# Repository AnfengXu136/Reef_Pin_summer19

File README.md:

# D-SEA: The Depth-Sensor Enclosed Application
## Project Overview
### Abstract
Depth information is crucial in the creation of underwater 3D interactive models. Divers and researchers need depth measurements to accurately depict the structure and levels of underwater architectures for a virtual reality marine ecosystem. Currently, divers are manually measuring the depth using dive watches, but this method is inconsistent because of variable depth readings caused by changing wave heights and human errors.  To combat these problems, we created Depth-Sensor Enclosed Application (D-SEA) to automatically collect and average pressure data while displaying the calculated depth readings with values up to 30 meters underwater which is 3 times more than expected diving conditions. This device can be easily assembled with a cost of under one-hundred dollars.  Building from past developments, we are working on an affordable, waterproof prototype with a display that is readable underwater, an automatic transition between on and off states when submerged in seawater, and automatic data logging onto an SD card. From testing the recent prototype in a pool, results show that the D-SEA is able to accurately calculate the depth and display it on the screen.

### 100 Island Challenge
Our project falls within the greater context of the 100 Island Challenge, headed by the Scripps Institute of Oceanography. The 100 Island Challenge is a project that is collecting photographic, geographic, and oceanographic data in order to build models of coral reef communities around the world and track their changes in structure and growth over time. More information on the challenge can be found [here](http://100islandchallenge.org/).

### Requirements
Researchers from Scripps Institution of Oceanography wish to work with this device under the following conditions: Bring the device on a boat and turn it on before going diving with the corals. Then they dive down and place the devices on the coral reef, and the device starts collecting depth information and displaying it on the screen. The divers swim back and forth to do the photomosaic survey, capturing images of the devices and the data shown on the screen. After that, they collect the devices and return to the boat. They read the data from the devices and download it for backup. Finally, they turn off the device and charge the device overnight.

### Objectives
Based on the requirements from Scripps Institution of Oceanography, we are building a device that can measure and display depth information when it’s placed on coral reefs. Then the depth information could be captured by cameras and retrieved from images. The other detailed functions are described as follows.
* Switch: A switch is needed to make sure the device can turn on before diving and turn off when it’s back to land. 
* Waterproof: Since the device needs to be working under 10-15 meters of salt water for around 4 hours, it should be strictly waterproof to avoid erosion. Waterproof also means that there may not be any buttons or plugs on this device.
* Clear display: The device works in relatively shallow, high-illumination conditions in coral reef communities. There will be sunlight, wind, and wave changing over time. The display module should display the depth information as clear as possible under different conditions to make sure the information can be retrieved from the images accurately.
* Rechargeable: The device needs to be reusable and rechargeable. The battery needs to be working for around 4 hours and can be charged fully over one night.
* Data storage: There may be cases that researchers fail to retrieve accurate depth information from unclear images. For backup consideration, this device should be integrated with a data storage module such as an SD-card.

### Previous Work
GitHub repositories containing work done by the previous teams on this project can be found here. Their works and documentations provided us with valuable guidance for this project.
* [Summer 2018 REU](https://github.com/UCSD-E4E/coral-reef-mapping)
* [Spring 2019 Quarter](https://github.com/ChenLR/SIT)

## Team Members (Summer 2019 Engineers for Exploration)
* Anfeng Xu - UC San Diego
* Brian Sebastian - UC San Diego
* Charmaine Beluso - Mississippi State University
* Eamon Patamasing - UC San Diego

## Resources
* [User Manual](https://docs.google.com/document/d/1ufcVEwToTL347TIJa8BTdMBOQnbh-Dc6tYHnt09aWhc/edit?usp=sharing)
* [Final Report](https://docs.google.com/document/d/1GHIrqxifWv97SIiYkwtMFNrA6XIQ8vvvFCd0-GAbfDE/edit?usp=sharing)
* [Technical Paper]()
* [Final Presentation](https://docs.google.com/presentation/d/16IRXAvVATnhi6VliVaiazFm-Qb-JAyPtN_WVCFj1rOY/edit#slide=id.g3feb1946b7_17_0)
* [Notes for next team](https://docs.google.com/document/d/1U75X6sHqDsNa_K2ptZNxjGdgGvhvemMbGUb-xTKog6w/edit?usp=sharing)
* [Next steps](https://docs.google.com/document/d/1MVm5gGPROugtsDwmIqsRltZwrWXT1dNbkipjWg4ARCg/edit?usp=sharing)

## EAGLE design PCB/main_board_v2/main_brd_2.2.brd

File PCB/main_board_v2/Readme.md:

## PCB files for main board
Includes Eagle files(a .sch and a .brd file), a schematic pdf and a lbr folder containing additional libraries. coral_power.lbr is a custom library file.

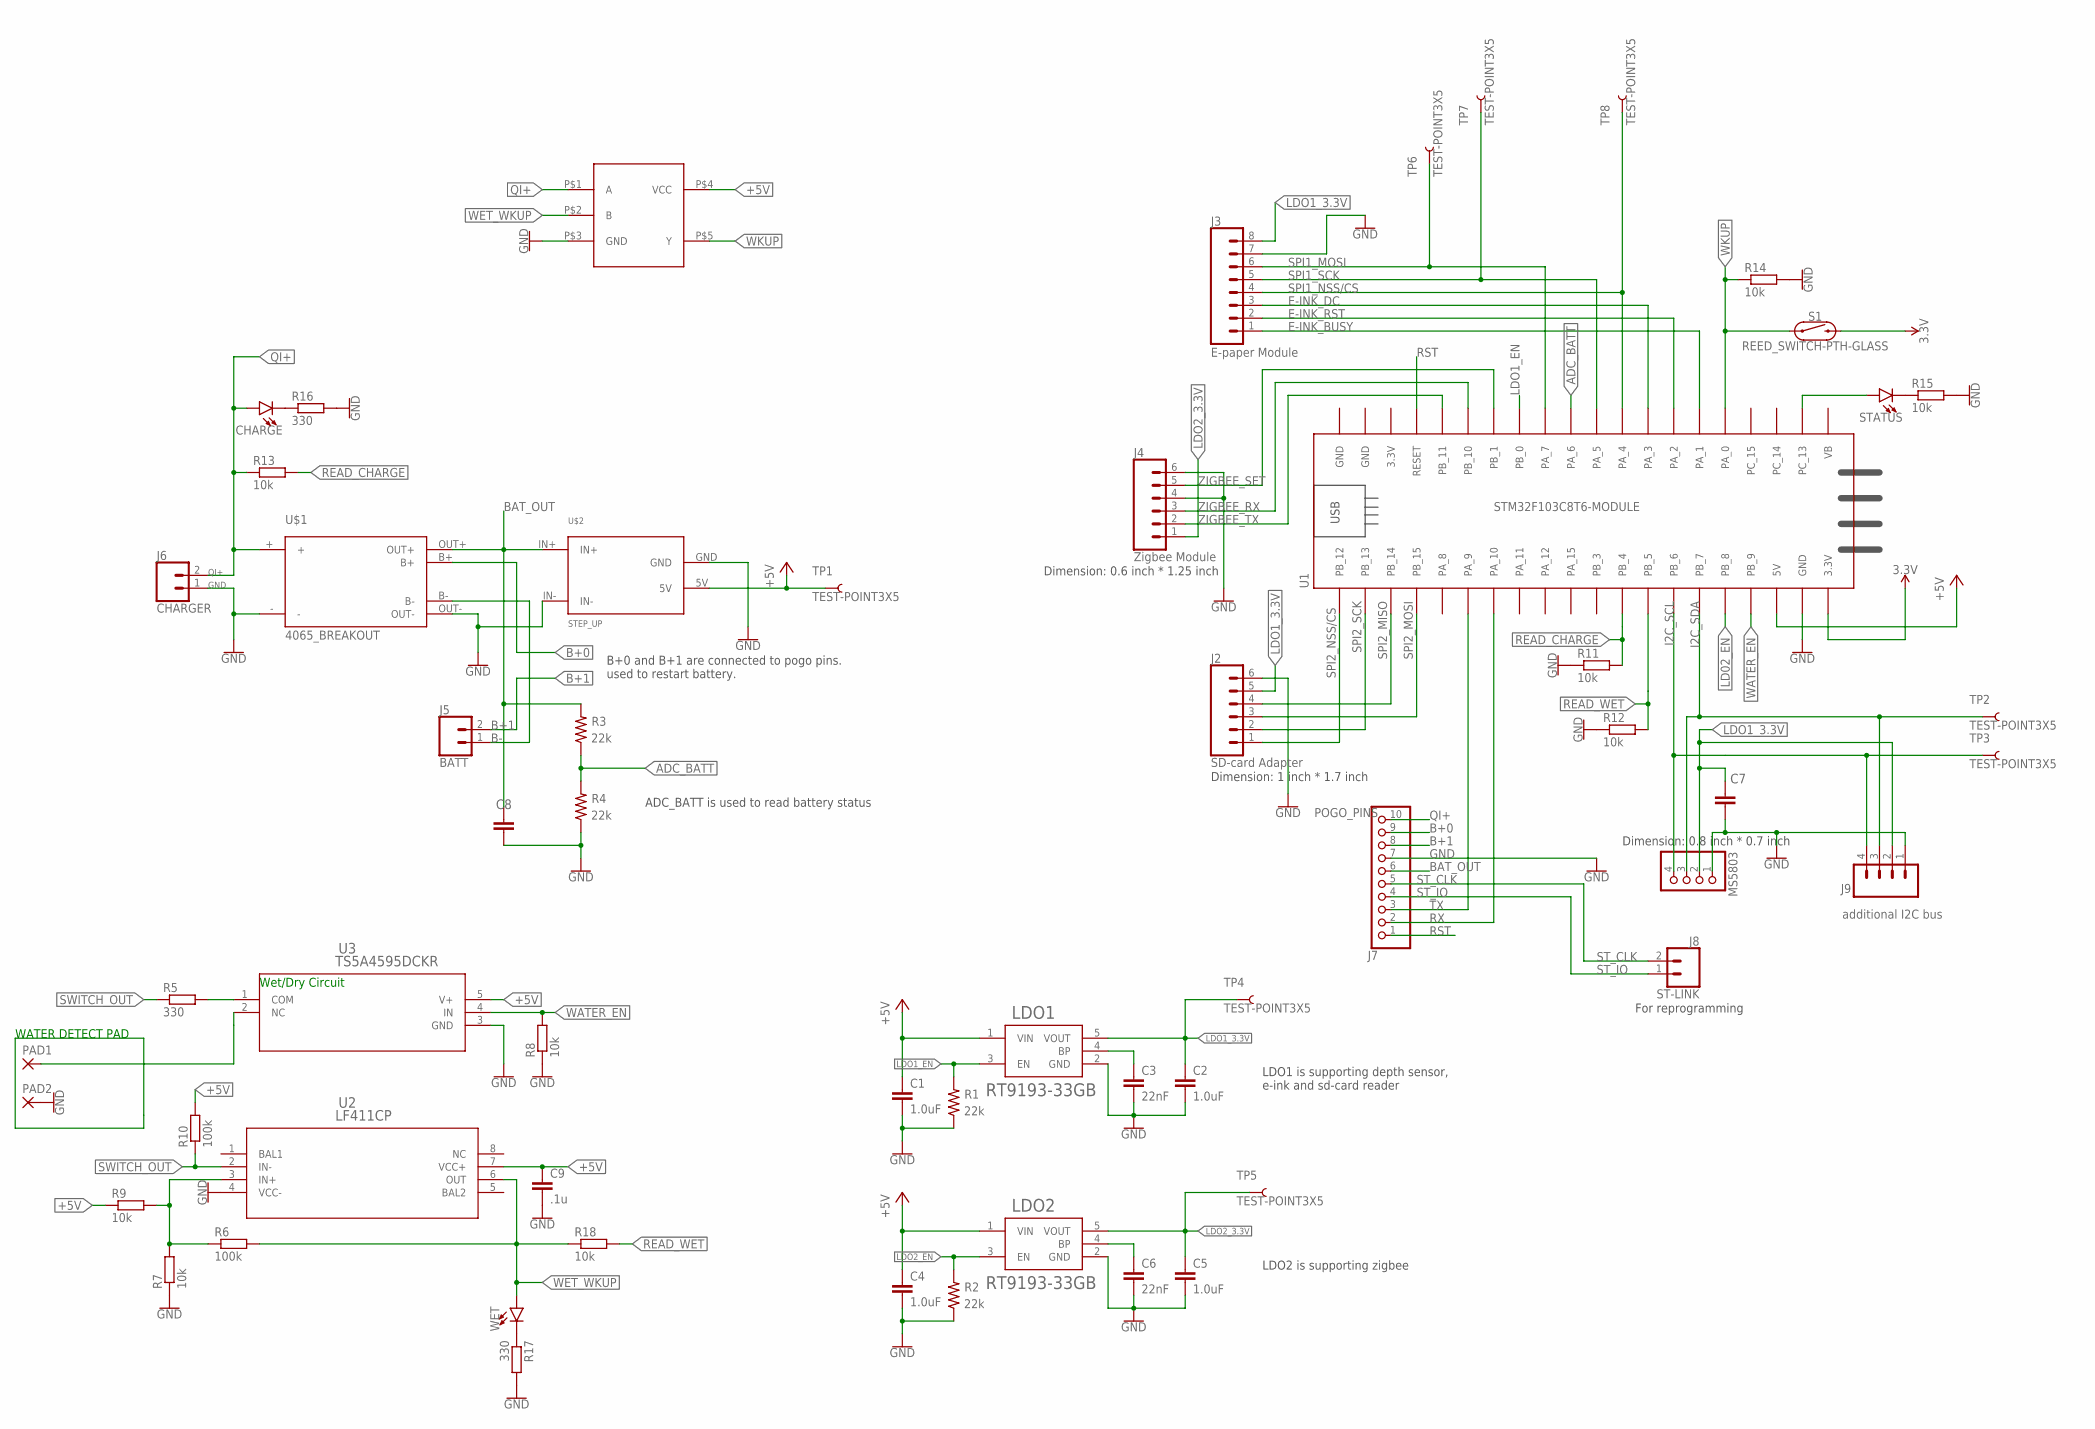
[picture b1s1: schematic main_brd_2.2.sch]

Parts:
C1, C2, C4, C5: 1.0uF; 0603
C3, C6: 22nF; 0603
C7: 100u; C025-050X050
C8: 220u; C025-050X050
C9: .1u; C0603
CHARGE: LED5MM; LED_5MM
J2: SD-card Adapter; 1X06
J3: E-paper Module; 1X08
J4: Zigbee Module; 1X06
J5: BATT; 1X02
J6: CHARGER; 1X02
J7: POGO_PINS; 1X10
J8: ST-LINK; 1X02
J9: additional I2C bus; 1X04
LDO1, LDO2: RT9193-33GB; SOT94P279X129-5N
MS5803: PINHD-1X4/90; 1X04/90
PAD1, PAD2: 3,81/1,4
R1, R2, R3, R4: 22k; 0603
R5, R16, R17: 330; R0603
R6, R10: 100k; R0603
R7, R8, R9, R11, R12, R13, R14, R15, R18: 10k; R0603
S1: REED_SWITCH-PTH-GLASS; REED_SWITCH_GLASS
STATUS: LED5MM; LED_5MM
TP1, TP2, TP3, TP4, TP5, TP6, TP7, TP8: TEST-POINT3X5; PAD.03X.05
U1: STM32F103C8T6-MODULE
U2: LF411CP; P8
U3: TS5A4595DCKR; DCK5
U$1: 4065_BREAKOUT; CHARGE_MODULE
U$2: STEP_UP; STEP_UP_99_69
U$3: 74LVC1G86SE-7; SOT25
WET: LED5MM; LED_5MM

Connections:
3.3V: S1.P$2 (2), U1.3.3V_1 (3.3V)
+5V: C1.1, C4.1, C9.1, LDO1.1 (VIN), LDO2.1 (VIN), R9.1, R10.2, TP1.P$1, U1.5V, U2.7 (VCC+), U3.5 (V+), U$2.5V, U$3.P$4 (VCC)
ADC_BATT: R3.1, R4.2, U1.PA_6
B+0: J7.9, U$1.B+
B+1: J5.2, J7.8
B-: J5.1, U$1.B-
BAT_OUT: C8.1, J7.6, R3.2, U$1.OUT+, U$2.IN+
E-INK_BUSY: J3.1, U1.PA_1
E-INK_DC: J3.3, U1.PA_3
E-INK_RST: J3.2, U1.PA_2
GND: C1.2, C2.2, C3.2, C4.2, C5.2, C6.2, C7.2, C8.2, C9.2, J2.6, J3.7, J4.4, J4.6, J6.1, J7.7, J9.1, LDO1.2 (GND), LDO2.2 (GND), MS5803.1, PAD2.1, R1.1, R2.1, R4.1, R7.1, R8.1, R11.1, R12.1, R14.2, R15.2, R16.2, R17.2, U1.GND_1 (GND), U1.GND_3 (GND), U2.4 (VCC-), U3.3 (GND), U$1.-, U$1.OUT-, U$2.GND, U$2.IN-, U$3.P$3 (GND)
I2C_SCL: J9.4, MS5803.4, TP3.P$1, U1.PB_6
I2C_SDA: J9.3, MS5803.3, TP2.P$1, U1.PB_7
LD02_EN: U1.PB_8
LDO1_3.3V: C2.1, C7.1, J2.5, J3.8, J9.2, LDO1.5 (VOUT), MS5803.2, TP4.P$1
LDO1_EN: LDO1.3 (EN), R1.2, U1.PB_0
LDO2_3.3V: C5.1, J4.1, LDO2.5 (VOUT), TP5.P$1
LDO2_EN: LDO2.3 (EN), R2.2
unnamed: C6.1, LDO2.4 (BP)
unnamed: C3.1, LDO1.4 (BP)
unnamed: CHARGE.K (C), R16.1
unnamed: R5.2, U3.1 (COM)
unnamed: R6.1, R7.2, R9.2, U2.3 (IN+)
unnamed: STATUS.A, U1.PC_13
unnamed: R15.1, STATUS.K (C)
unnamed: PAD1.1, U3.2 (NC)
unnamed: R17.1, WET.K (C)
QI+: CHARGE.A, J6.2, J7.10, R13.1, U$1.+, U$3.P$1 (A)
READ_CHARGE: R11.2, R13.2, U1.PB_4
READ_WET: R12.2, R18.2, U1.PB_5
RST: J7.1, U1.RESET
RX: J7.2, U1.PA_10
SPI1_MOSI: J3.6, TP6.P$1, U1.PA_7
SPI1_NSS/CS: J3.4, TP8.P$1, U1.PA_4
SPI1_SCK: J3.5, TP7.P$1, U1.PA_5
SPI2_MISO: J2.4, U1.PB_14
SPI2_MOSI: J2.3, U1.PB_15
SPI2_NSS/CS: J2.1, U1.PB_12
SPI2_SCK: J2.2, U1.PB_13
ST_CLK: J7.5, J8.2
ST_IO: J7.4, J8.1
SWITCH_OUT: R5.1, R10.1, U2.2 (IN-)
TX: J7.3, U1.PA_9
WATER_EN: R8.2, U1.PB_9, U3.4 (IN)
WET_WKUP: R6.2, R18.1, U2.6 (OUT), U$3.P$2 (B), WET.A
WKUP: R14.1, S1.P$1 (1), U1.PA_0, U$3.P$5 (Y)
ZIGBEE_RX: J4.3, U1.PB_10
ZIGBEE_SET: J4.5, U1.PB_1
ZIGBEE_TX: J4.2, U1.PB_11

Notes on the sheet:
E-paper Module
For reprogramming
LDO1 is supporting depth sensor, e-ink and sd-card reader
LDO2 is supporting zigbee
ADC_BATT is used to read battery status
B+0 and B+1 are connected to pogo pins. used to restart battery.
Dimension: 1 inch * 1.7 inch
Dimension: 0.8 inch * 0.7 inch
Dimension: 0.6 inch * 1.25 inch
Wet/Dry Circuit
WATER DETECT PAD

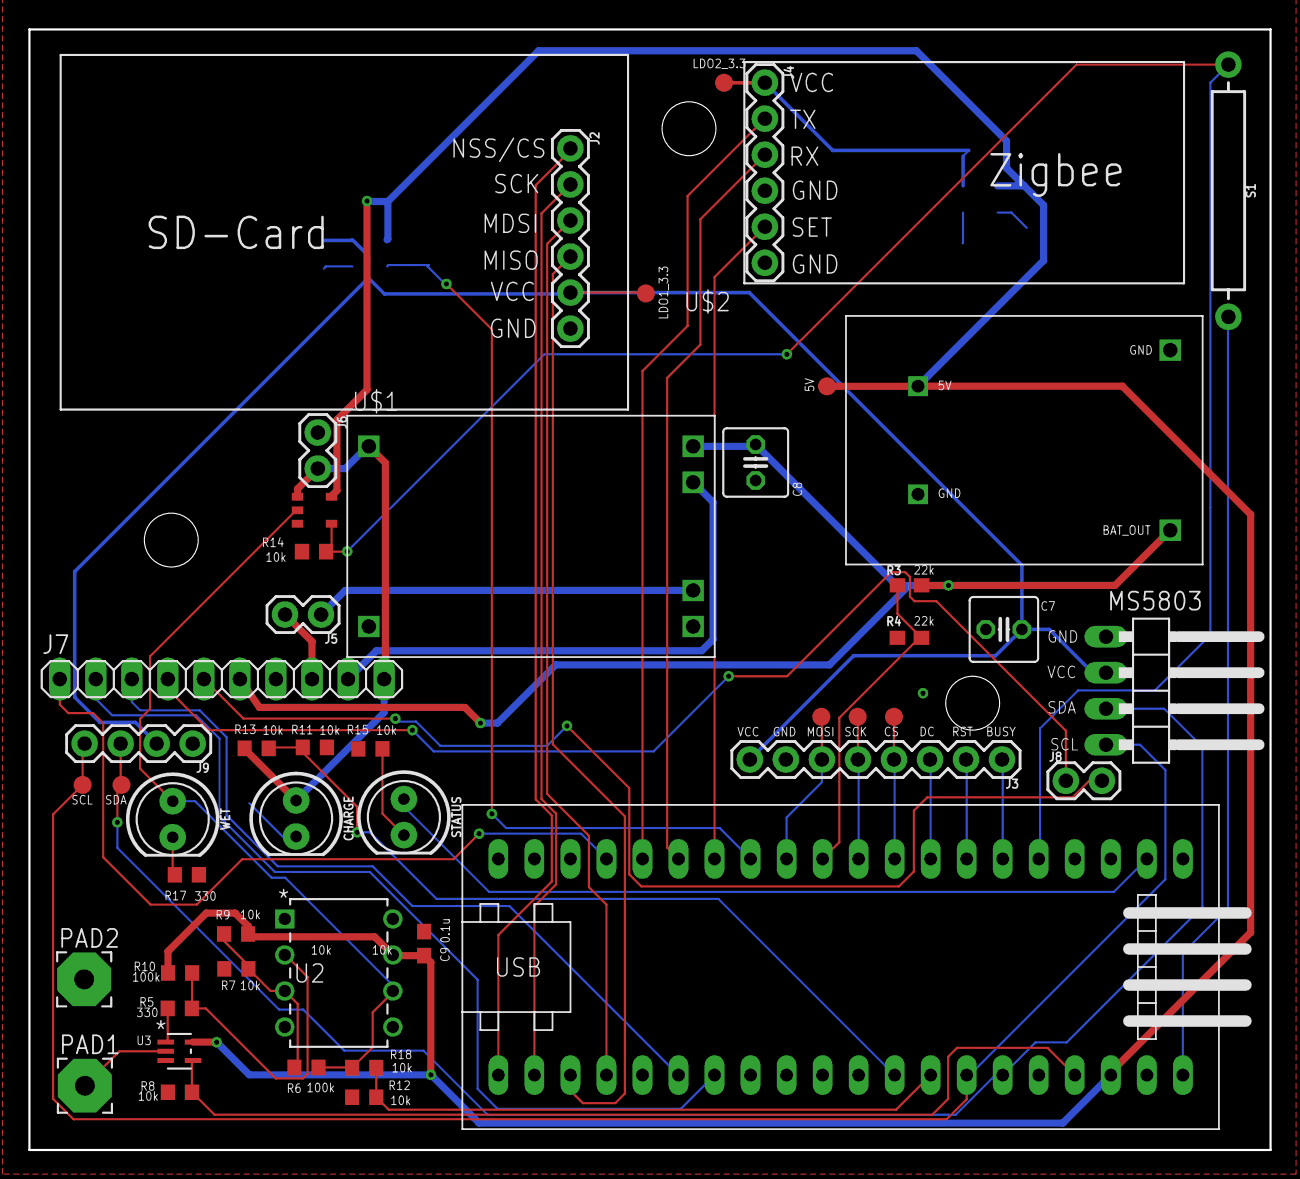
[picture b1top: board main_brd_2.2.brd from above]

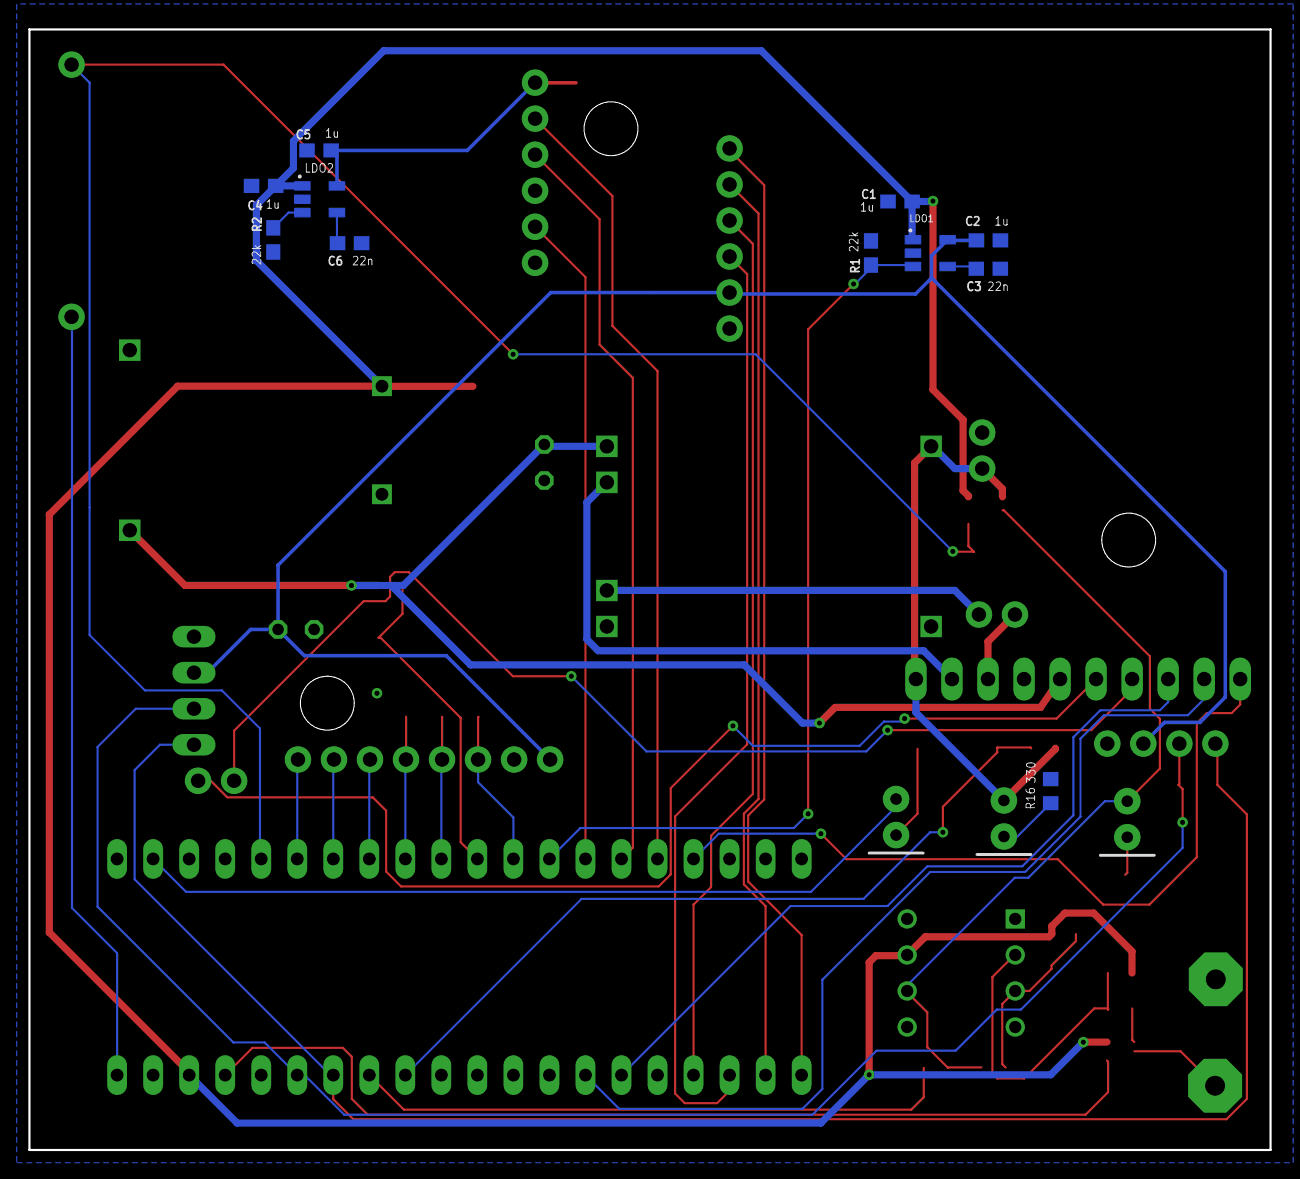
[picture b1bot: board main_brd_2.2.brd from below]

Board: 2 copper layers, 87.5 x 79.0 mm, 58 parts (11 on the bottom side), 48 nets.

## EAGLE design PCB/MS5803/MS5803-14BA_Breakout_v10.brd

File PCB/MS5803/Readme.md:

### PCB files for MS5803 Breakout design
A .sch, a .brd and a pcb Gerber zip file are included.

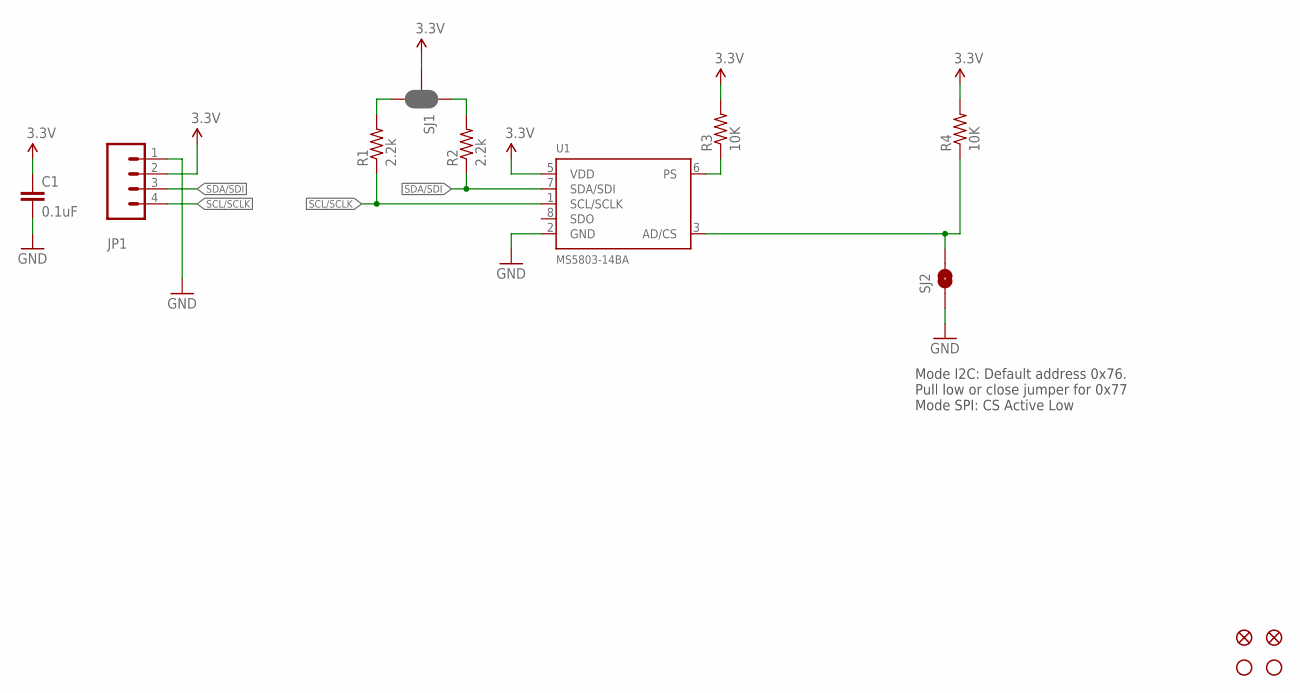
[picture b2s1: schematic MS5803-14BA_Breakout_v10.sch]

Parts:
C1: 0.1uF; 0603-CAP
FID1, FID2: FIDUCIAL1X2; FIDUCIAL-1X2
JP1: CONN_04PTH; 1X04
R1, R2: 2.2k; 0603-RES
R3, R4: 10K; 0603-RES
SJ1: JUMPER-PAD-3-NC_BY_PASTE; PAD-JUMPER-3-NC_BY_PASTE_YES_SILK_FULL_BOX
SJ2: SOLDERJUMPERNO; SJ_2S-NO
STANDOFF1, STANDOFF2: STAND-OFFTIGHT; STAND-OFF-TIGHT
U1: MS5803-14BA; MS5803

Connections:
3.3V: C1.1, JP1.2, R3.2, R4.2, SJ1.2, U1.5 (VDD)
AD/CS: R4.1, SJ2.2, U1.3 (AD/CS)
GND: C1.2, JP1.1, SJ2.1, U1.2 (GND)
unnamed: R1.2, SJ1.3
unnamed: R2.2, SJ1.1
PS: R3.1, U1.6 (PS)
SCL/SCLK: JP1.4, R1.1, U1.1 (SCL/SCLK)
SDA/SDI: JP1.3, R2.1, U1.7 (SDA/SDI)

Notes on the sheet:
Mode I2C: Default address 0x76. Pull low or close jumper for 0x77 Mode SPI: CS Active Low

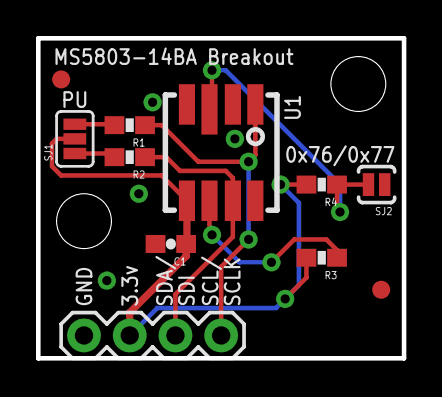
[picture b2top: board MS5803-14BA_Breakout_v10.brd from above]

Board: 2 copper layers, 20.3 x 17.8 mm, 13 parts (0 on the bottom side), 8 nets.

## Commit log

2019-06-25 coppied from SIT team
2019-07-01 added I2C bus to the schematic and did the routing for the PCB board
2019-07-02 updated board
2019-07-02 implemented the sleep mode
2019-07-05 finalized PCB and updated the Voltage reading methodology
2019-07-05 this version is for implemating the 3 states, wet/standby/charging
2019-07-06 changed configuraration
2019-07-06 changed wakeup/standby setting suited to wet/dry system: turn on when PA1 High and turn off when PA1 LOW
2019-07-08 code for new lcd
2019-07-08 Added Init_Check_Status
2019-07-09 some indentation
2019-07-09 changed the main function and added charging state
2019-07-09 changed the charging display
2019-07-09 added turn on/off for LCD2
2019-07-09 New LCD Definition in Code
2019-07-11 added averaging functionality, still incomplete
2019-07-12 new PCB version
2019-07-12 added water enable pin
2019-07-12 disable interrupt when in water
2019-07-16 fixed build errors
2019-07-24 Added PCB for version 3
2019-07-29 this version is integrated for data logging
2019-07-29 clearing e-ink 1 sec before
2019-08-02 Separated file names
2019-08-07 Changed file type to .csv and disabled LFN
2019-08-09 Added version 2.2 of board
2019-08-12 updated clearing display
2019-08-12 Created board 2.2
2019-08-13 Fixed wkup and routing
2019-08-19 Update README.md for D-SEA
2019-08-20 Added SD card error messages to E-Ink
2019-08-20 Add files via upload
    a new readme for general software
2019-08-23 Added gerber files
2019-08-23 Added CAD files for box mount
2019-08-23 Modified pin height
2019-08-26 added clearing e-ink
2019-08-26 Fixed total height and tolerances
2019-08-26 Update README.md
    added notes links

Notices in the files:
parts and their libraries:
SparkFun-Aesthetics: Licensing: Creative Commons ShareAlike 4.0 International - https://creativecommons.org/licenses/by-sa/4.0
